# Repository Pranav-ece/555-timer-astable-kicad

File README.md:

# 555-timer-astable-kicad
KiCad-based PCB design of a 555 Timer astable multivibrator generating square wave output, with full design files and documentation.”

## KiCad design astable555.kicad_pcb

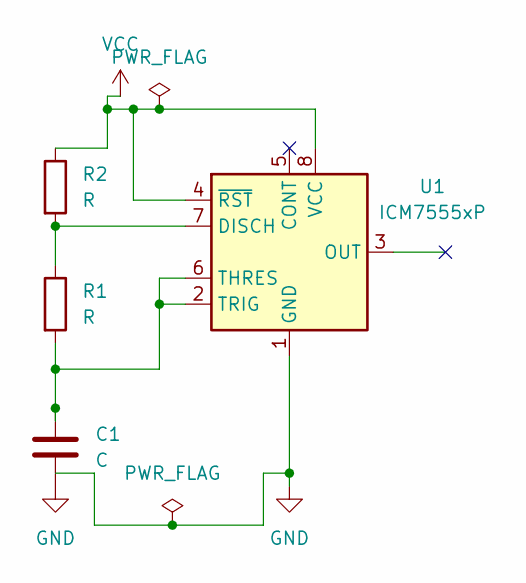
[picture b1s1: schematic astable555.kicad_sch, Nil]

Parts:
C1: C; CP_Axial_L18.0mm_D8.0mm_P25.00mm_Horizontal
R1: R; R_Axial_DIN0411_L9.9mm_D3.6mm_P7.62mm_Vertical
R2: R; R_Axial_DIN0411_L9.9mm_D3.6mm_P20.32mm_Horizontal
U1: ICM7555xP; DIP-8_W7.62mm

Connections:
GND: C1.2, U1.1 (GND)
unnamed: R1.1, R2.2, U1.7 (DISCH)
unnamed: C1.1, R1.2, U1.2 (TRIG), U1.6 (THRES)
VCC: R2.1, U1.4 (~RST), U1.8 (VCC)

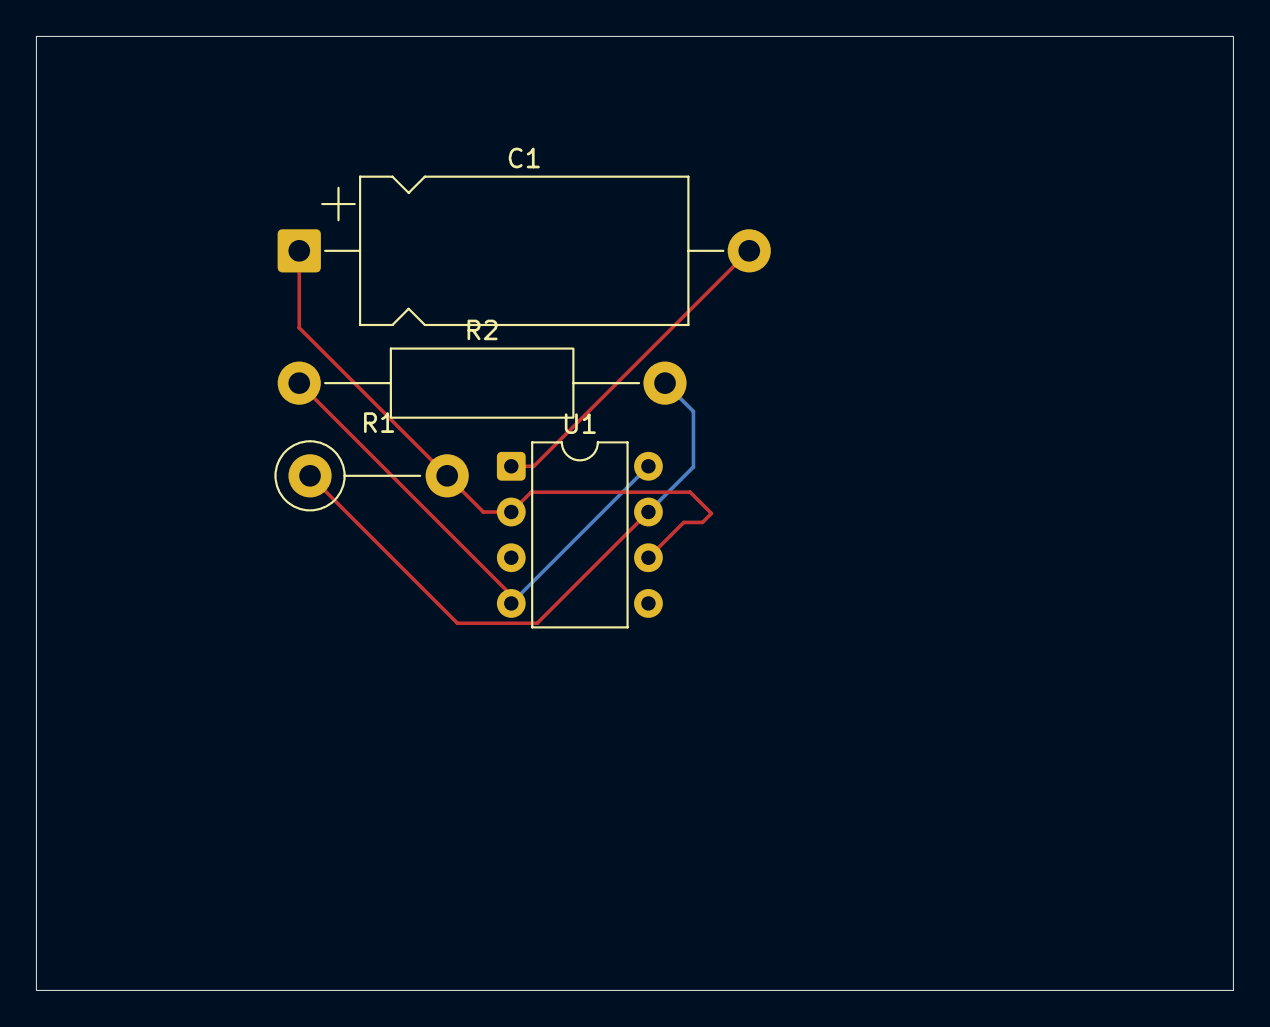
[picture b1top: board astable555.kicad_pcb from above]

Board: 2 copper layers, 66.5 x 53.0 mm, 4 parts (0 on the bottom side), 4 nets.
